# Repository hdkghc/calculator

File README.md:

[中文](README_zh.md)

# Calculator \| Operator Lambda

A scientific/graphical calculator firmware for Raspberry Pi Pico, with CAS (Computer Algebra System) and graphical display support.

PCB Preview ---->

**Status**: Under active development. Core CAS and display subsystem are partially implemented; basic arithmetic, expression parsing, and simplification are functional. Integration and matrix operations are in progress.

---

## Features

- CAS core: expression parsing, simplification, differentiation, integration (partial), rational arithmetic, symbolic manipulation.
- Display: 1.8" ST7735 TFT (160×128) with custom font rendering (ClassWiz-style fonts included).
- Input: 6×6 matrix keypad, debounced and mapped to mathematical operators.
- Storage: SD card support (WIP) for program/data loading.
- Modular design: separated CAS, display interface, input handling, and hardware abstraction.

---

## Hardware Requirements

- MCU: Raspberry Pi Pico (primary), Arduino Nano (power/control)
- Display: ST7735-based 1.8" TFT (SPI, with optional SD slot)
- Keypad: 6×6 matrix keypad (custom PCB – see `hardware/kicad` directory)
- Optional: SD card module (SPI)

Refer to `wiring.txt` (deprecated) and `hardware/kicad/` for schematics and PCB design. Gerber files are available in `hardware/gerber*.zip`.

---

## Project Structure

```
calculator/
├── CMakeLists.txt          # Build configuration
├── build.sh                # Convenience build script
├── inc/                    # Header files
│   ├── cas/                # CAS core (parser, simplifier, integrator, etc.)
│   └── dispinterface/      # Display abstraction
├── src/                    # Source files
│   ├── main.cpp            # Entry point
│   └── cas/                # CAS implementation
├── fonts/                  # Generated font data (ClassWiz style)
├── font2h/                 # Font conversion tools (font2h, preview)
├── hardware/               # PCB design (KiCad, Fritzing(deprecated), Gerber)
├── test/                   # Unit tests (CAS functions)
├── resources/              # Images (logo, PCB preview)
└── LICENSE                 # GPLv3
```

---

## Build Instructions

1. Install the [Raspberry Pi Pico SDK](https://github.com/raspberrypi/pico-sdk) and toolchain (arm-none-eabi-g++, CMake).
2. Clone this repository:
   ```
   git clone https://github.com/hdkghc/calculator.git
   cd calculator
   ```
3. Build:
   - Recommended: run `./build.sh` (automates CMake configuration and build).
   - Manual:
     ```
     mkdir build && cd build
     cmake ..
     make
     ```
4. Flash: drag the generated `.uf2` file to your Pico's mass storage device, or use `picotool`.

---

## Dependencies

- Raspberry Pi Pico SDK (required)
- C++17 compiler (`arm-none-eabi-g++`)

---

## License

This project is licensed under the **GNU General Public License v3.0**.  
See [LICENSE](LICENSE) for details.

---

## Disclaimer

This is an amateur, non-commercial open‑source project. All hardware and software are provided “as is”, without any warranty. The author assumes no liability for any damage or injury resulting from the use, assembly, or modification of this project.

---

## Contributing

Contributions are welcome! Please read [CONTRIBUTING.md](CONTRIBUTING.md) for guidelines.

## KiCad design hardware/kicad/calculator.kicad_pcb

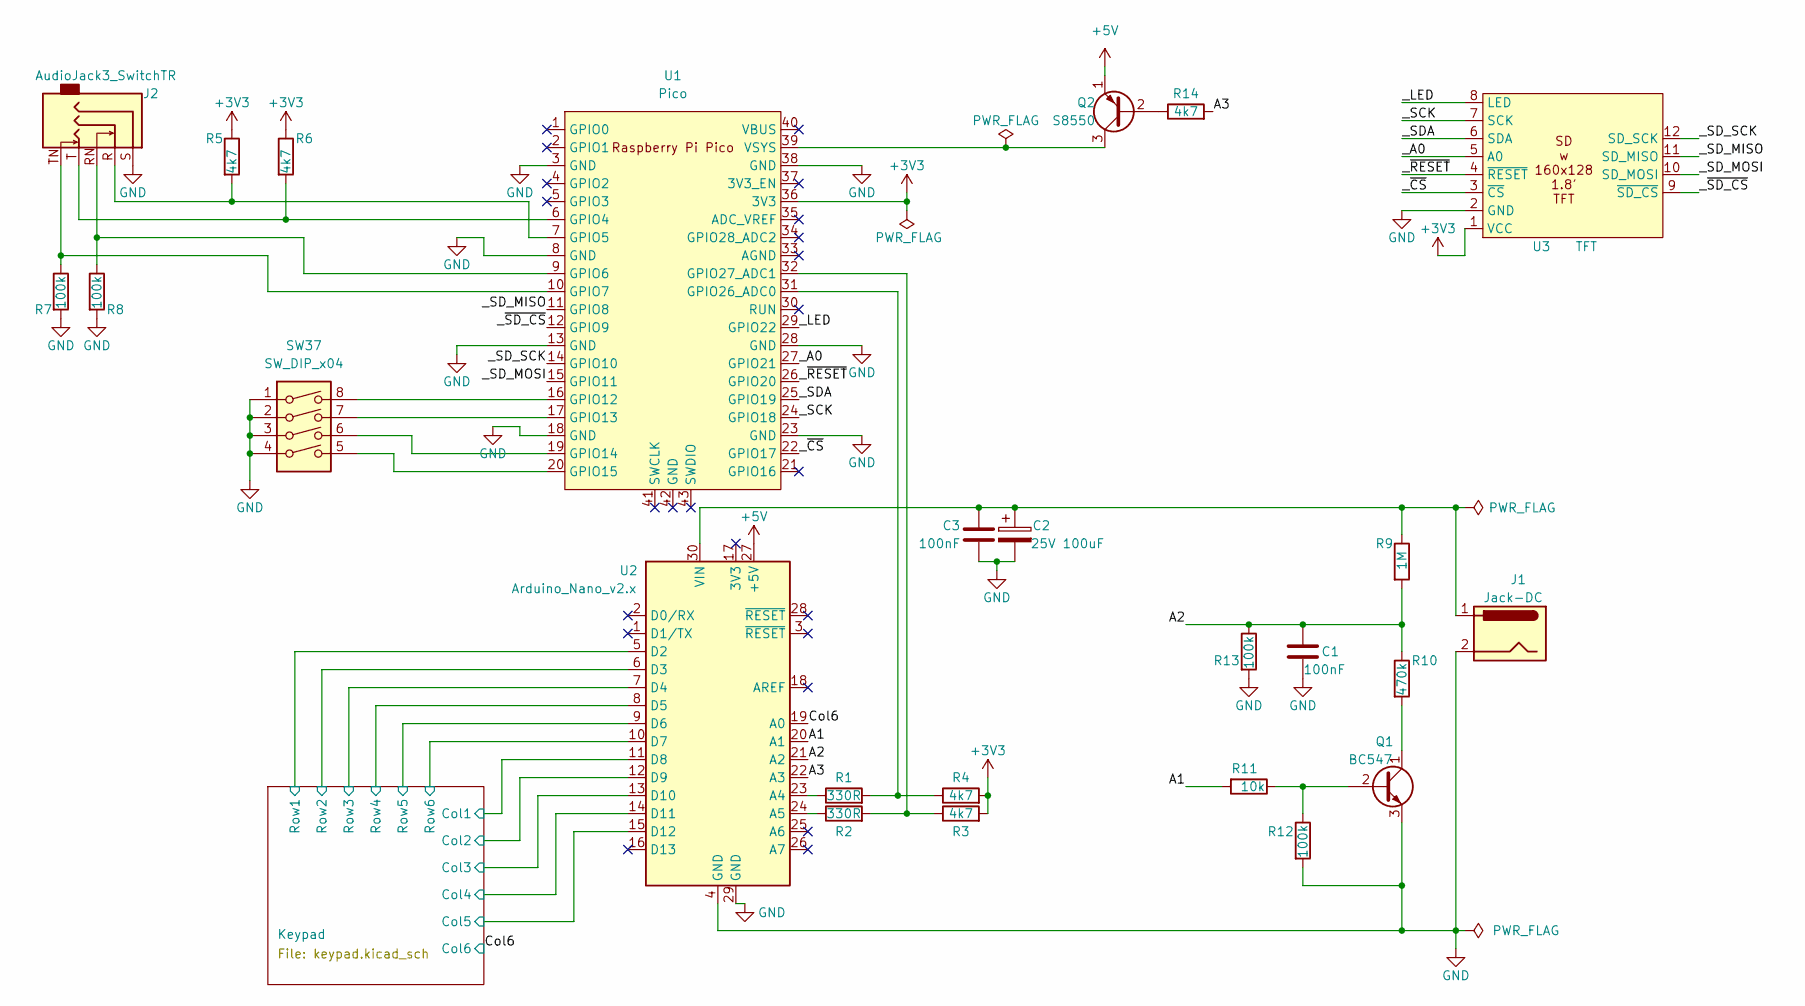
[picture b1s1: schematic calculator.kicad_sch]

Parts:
C1: 100nF; C_Disc_D6.0mm_W2.5mm_P5.00mm
C2: 25V 100uF; CP_Radial_D8.0mm_P3.50mm
C3: 100nF; C_Disc_D7.0mm_W2.5mm_P5.00mm
J1: Jack-DC; BarrelJack_Kycon_KLDX-0202-xC_Horizontal
J2: AudioJack3_SwitchTR; Jack_3.5mm_CUI_SJ1-3525N_Horizontal
Q1: BC547; TO-92_Inline
Q2: S8550; TO-92_Inline
R1, R2: 330R; R_Axial_DIN0207_L6.3mm_D2.5mm_P10.16mm_Horizontal
R3, R4, R5, R6, R14: 4k7; R_Axial_DIN0207_L6.3mm_D2.5mm_P10.16mm_Horizontal
R7, R8, R12, R13: 100k; R_Axial_DIN0207_L6.3mm_D2.5mm_P10.16mm_Horizontal
R9: 1M; R_Axial_DIN0207_L6.3mm_D2.5mm_P10.16mm_Horizontal
R10: 470k; R_Axial_DIN0207_L6.3mm_D2.5mm_P10.16mm_Horizontal
R11: 10k; R_Axial_DIN0207_L6.3mm_D2.5mm_P10.16mm_Horizontal
SW37: SW_DIP_x04; SW_DIP_SPSTx04_Slide_6.7x11.72mm_W7.62mm_P2.54mm_LowProfile
U1: Pico; RPi_Pico_SMD_TH
U2: Arduino_Nano_v2.x; Arduino_Nano
U3: TFT; MSP1803_TFT_12pin

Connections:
+3V3: R3.2, R4.2, R5.1, R6.1, U1.36 (3V3), U3.1 (VCC)
+5V: Q2.1 (E), U2.27 (+5V)
/A1: R11.2, U2.20 (A1)
/A2: C1.1, R9.2, R10.1, R13.1, U2.21 (A2)
/A3: R14.2, U2.22 (A3)
/Col6: U2.19 (A0); also elsewhere on the board
/Keypad/Col1: U2.11 (D8); also elsewhere on the board
/Keypad/Col2: U2.12 (D9); also elsewhere on the board
/Keypad/Col3: U2.13 (D10); also elsewhere on the board
/Keypad/Col4: U2.14 (D11); also elsewhere on the board
/Keypad/Col5: U2.15 (D12); also elsewhere on the board
/Keypad/Row1: U2.5 (D2); also elsewhere on the board
/Keypad/Row2: U2.6 (D3); also elsewhere on the board
/Keypad/Row3: U2.7 (D4); also elsewhere on the board
/Keypad/Row4: U2.8 (D5); also elsewhere on the board
/Keypad/Row5: U2.9 (D6); also elsewhere on the board
/Keypad/Row6: U2.10 (D7); also elsewhere on the board
/_A0: U1.27 (GPIO21), U3.5 (A0)
/_LED: U1.29 (GPIO22), U3.8 (LED)
/_SCK: U1.24 (GPIO18), U3.7 (SCK)
/_SDA: U1.25 (GPIO19), U3.6 (SDA)
/_SD_MISO: U1.11 (GPIO8), U3.11 (SD_MISO)
/_SD_MOSI: U1.15 (GPIO11), U3.10 (SD_MOSI)
/_SD_SCK: U1.14 (GPIO10), U3.12 (SD_SCK)
/_~CS: U1.22 (GPIO17), U3.3 (~CS)
/_~RESET: U1.26 (GPIO20), U3.4 (~RESET)
/_~SD_CS: U1.12 (GPIO9), U3.9 (~SD_CS)
GND: C1.2, C2.2, C3.1, J1.2, J2.S, Q1.3 (E), R7.2, R8.2, R12.2, R13.2, SW37.1, SW37.2, SW37.3, SW37.4, U1.3 (GND), U1.8 (GND), U1.13 (GND), U1.18 (GND), U1.23 (GND), U1.28 (GND), U1.38 (GND), U2.4 (GND), U2.29 (GND), U3.2 (GND)
unnamed: Q1.2 (B), R11.1, R12.1
unnamed: Q1.1 (C), R10.2
unnamed: Q2.2 (B), R14.1
unnamed: Q2.3 (C), U1.39 (VSYS)
unnamed: J2.T, R6.2, U1.6 (GPIO4)
unnamed: J2.R, R5.2, U1.7 (GPIO5)
unnamed: J2.RN, R8.1, U1.9 (GPIO6)
unnamed: J2.TN, R7.1, U1.10 (GPIO7)
unnamed: SW37.8, U1.16 (GPIO12)
unnamed: SW37.7, U1.17 (GPIO13)
unnamed: SW37.6, U1.19 (GPIO14)
unnamed: SW37.5, U1.20 (GPIO15)
unnamed: R1.2, R4.1, U1.31 (GPIO26_ADC0)
unnamed: R2.2, R3.1, U1.32 (GPIO27_ADC1)
unnamed: R1.1, U2.23 (A4)
unnamed: R2.1, U2.24 (A5)
unnamed: C2.1, C3.2, J1.1, R9.1, U2.30 (VIN)

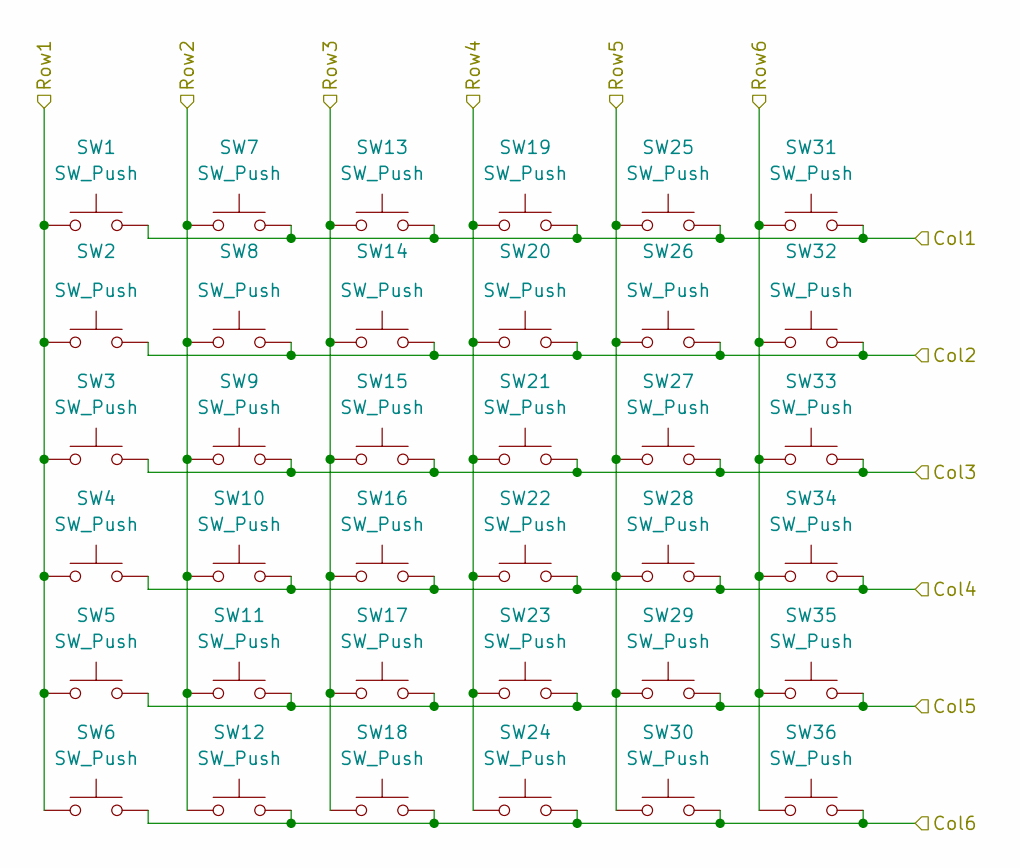
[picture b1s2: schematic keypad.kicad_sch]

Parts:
SW1, SW2, SW3, SW4, SW5, SW6, SW7, SW8, SW9, SW10, SW11, SW12, SW13, SW14, SW15, SW16, SW17, SW18, SW19, SW20, SW21, SW22, SW23, SW24, SW25, SW26, SW27, SW28, SW29, SW30, SW31, SW32, SW33, SW34, SW35, SW36: SW_Push; SW_PUSH_6mm

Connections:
/Col6: SW6.2, SW12.2, SW18.2, SW24.2, SW30.2, SW36.2; also elsewhere on the board
/Keypad/Col1: SW1.2, SW7.2, SW13.2, SW19.2, SW25.2, SW31.2; also elsewhere on the board
/Keypad/Col2: SW2.2, SW8.2, SW14.2, SW20.2, SW26.2, SW32.2; also elsewhere on the board
/Keypad/Col3: SW3.2, SW9.2, SW15.2, SW21.2, SW27.2, SW33.2; also elsewhere on the board
/Keypad/Col4: SW4.2, SW10.2, SW16.2, SW22.2, SW28.2, SW34.2; also elsewhere on the board
/Keypad/Col5: SW5.2, SW11.2, SW17.2, SW23.2, SW29.2, SW35.2; also elsewhere on the board
/Keypad/Row1: SW1.1, SW2.1, SW3.1, SW4.1, SW5.1, SW6.1; also elsewhere on the board
/Keypad/Row2: SW7.1, SW8.1, SW9.1, SW10.1, SW11.1, SW12.1; also elsewhere on the board
/Keypad/Row3: SW13.1, SW14.1, SW15.1, SW16.1, SW17.1, SW18.1; also elsewhere on the board
/Keypad/Row4: SW19.1, SW20.1, SW21.1, SW22.1, SW23.1, SW24.1; also elsewhere on the board
/Keypad/Row5: SW25.1, SW26.1, SW27.1, SW28.1, SW29.1, SW30.1; also elsewhere on the board
/Keypad/Row6: SW31.1, SW32.1, SW33.1, SW34.1, SW35.1, SW36.1; also elsewhere on the board

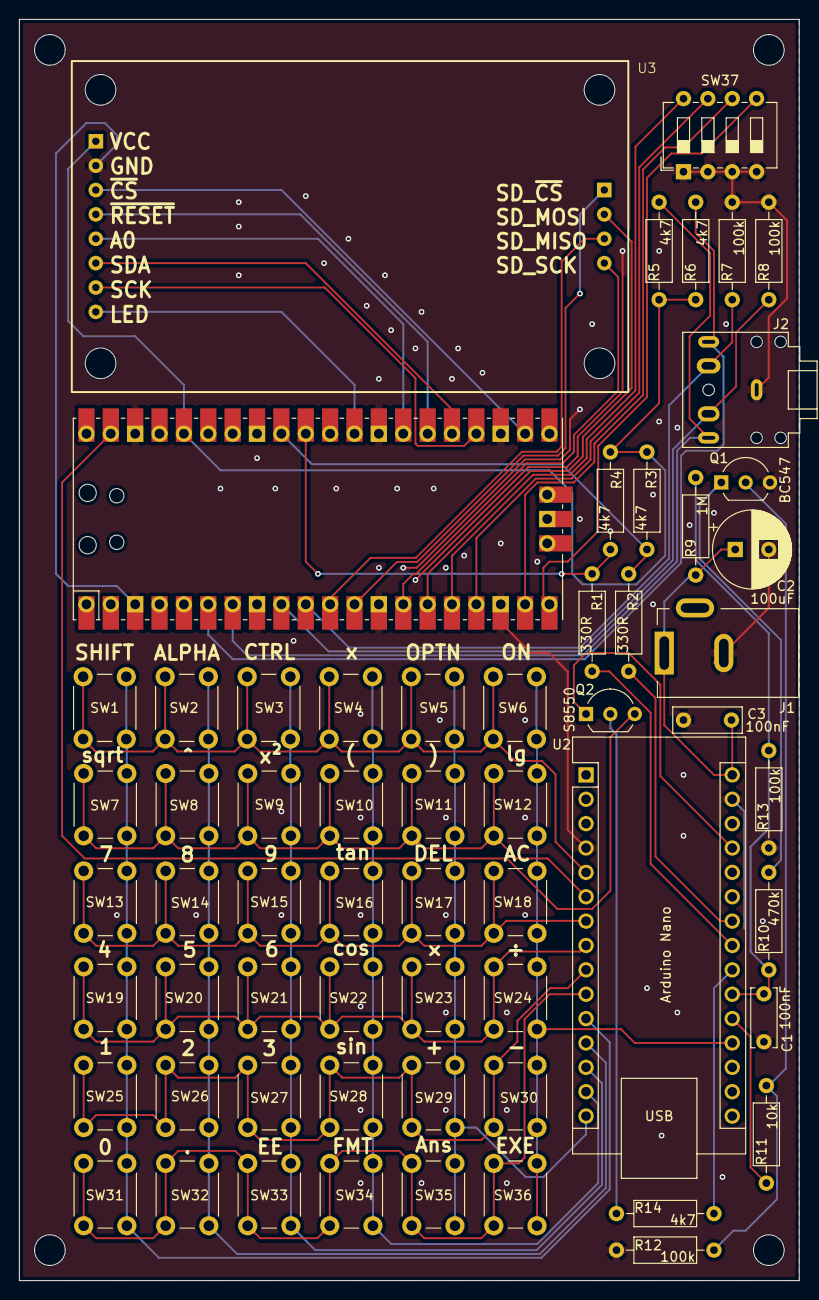
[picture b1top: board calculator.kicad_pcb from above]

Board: 2 copper layers, 81.3 x 131.4 mm, 61 parts (0 on the bottom side), 45 nets.

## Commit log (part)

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2026-04-20 new file: .gitignore new file: CMakeLists.txt new file: build.sh new file: main.cpp copy file: pico_sdk_import.cmake
2026-04-20 modified: CMakeLists.txt
2026-04-20 modified: .gitignore new file: .gitmodules modified: CMakeLists.txt
2026-04-25 modified: .gitignore new file: wiring.txt
2026-04-25 modified: .gitignore modified: CMakeLists.txt modified: build.sh new file: font2h/compile.sh new file: font2h/font2h.cpp new file: font2h/fonts/ClassWizCWDisplay-Regular.otf new file: font2h/fonts/Cl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
2026-04-25 modified: .gitignore modified: build.sh modified: font2h/compile.sh deleted: font2h/pvw.cpp new file: inc/rgb.h modified: main.cpp new file: test_fonts/CMakeLists.txt new file: test_fonts/testbuild.s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
2026-04-25 modified: CMakeLists.txt modified: build.sh modified: font2h/compile.sh modified: main.cpp deleted: test_fonts/CMakeLists.txt deleted: test_fonts/testbuild.sh deleted: test_fonts/testmain.cpp
2026-04-25 new file: CONTRIBUTING.md new file: LICENSE new file: README.md modified: main.cpp
2026-04-25 modified: LICENSE
2026-04-26 modified: .gitignore modified: CMakeLists.txt modified: main.cpp modified: pico-st7735/lib-st7735/include/ST7735_TFT.h modified: pico-st7735/lib-st7735/src/ST7735_TFT.c
2026-05-17 modified: .gitmodules modified: CMakeLists.txt modified: inc/rgb.h deleted: main.cpp deleted: pico-st7735/ new file: src/display.cpp new file: src/main.cpp
2026-05-17 modified: CMakeLists.txt renamed: src/display.cpp -> inc/display.hpp modified: inc/rgb.h modified: src/main.cpp
2026-05-23 new file: inc/cas/intg.hpp modified: inc/display.hpp modified: inc/rgb.h modified: src/main.cpp
2026-05-23 modified: inc/cas/intg.hpp
2026-05-23 new file: inc/cas/gcd.hpp modified: inc/cas/intg.hpp modified: inc/display.hpp modified: inc/rgb.h modified: src/main.cpp
2026-05-23 modified: inc/cas/intg.hpp new file: inc/cas/rational.hpp
2026-05-24 bug fix modified: .gitignore new file: compile_test.sh modified: inc/cas/intg.hpp new file: test/testintg.cpp
2026-05-24 modified: test/testintg.cpp
2026-05-30 modified: inc/cas/intg.hpp modified: test/testintg.cpp
2026-06-06 Update README to include generation note
    Added a note indicating that the README was generated by GitHub Copilot.
2026-06-06 update: README.md
2026-06-26 Bug fix: class Intg constructor & operator+ modified: inc/cas/intg.hpp new file: test/test_intg_init.cpp new file: test/test_random_intg.cpp modified: test/testintg.cpp
2026-06-26 added basic rational calculations modified: inc/cas/intg.hpp modified: inc/cas/rational.hpp
2026-06-26 new file: inc/cas/exptree.hpp
2026-06-27 modified: inc/cas/exptree.hpp
2026-06-27 new file: inc/cas/expdef.hpp
2026-06-27 + Scientific constants modified: inc/cas/expdef.hpp
2026-06-27 + constant definitions new file: inc/cas/constdef.hpp modified: inc/cas/expdef.hpp
2026-06-27 modified: inc/cas/exptree.hpp new file: inc/cas/treesimp.hpp
2026-06-27 Expression tree simplify logic & integer sqrt modified: inc/cas/intg.hpp modified: inc/cas/rational.hpp modified: inc/cas/treesimp.hpp
2026-06-27 Upd: expression tree simplify logic modified: inc/cas/expdef.hpp modified: inc/cas/treesimp.hpp
2026-06-27 Upd comment modified: inc/cas/treesimp.hpp
2026-06-27 upd sqrt modified: inc/cas/intg.hpp
2026-06-28 modified: inc/cas/treesimp.hpp
2026-06-28 split treesimp.hpp into submodules new file: inc/cas/simp/exptreepool.hpp new file: inc/cas/simp/simp_internal.hpp new file: inc/cas/simp/simputil.hpp modified: inc/cas/treesimp.hpp new file: src/cas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
2026-06-28 complex number support modified: src/cas/simp/simp_arith.cpp modified: src/cas/simp/simp_log.cpp modified: src/cas/simp/simp_misc.cpp modified: src/cas/simp/simp_trig.cpp
2026-06-28 matrix & vector support modified: inc/cas/intg.hpp modified: inc/cas/simp/simputil.hpp modified: inc/cas/treesimp.hpp modified: src/cas/simp/simp_arith.cpp new file: src/cas/simp/simp_complex.cpp new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
2026-06-28 Update .gitmodules, display.hpp and one other file
2026-06-28 new file: test/test_treesimp.cpp new file: test/treesimp.txt modified: compile_test.sh modified: inc/cas/gcd.hpp modified: inc/cas/intg.hpp modified: inc/cas/treesimp.hpp modified: src/cas/simp/simp_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
2026-06-28 Updated exptree simplifier modified: src/cas/simp/simp_number.cpp modified: test/treesimp.txt
2026-06-28 Upd modified: src/cas/simp/simp_arith.cpp modified: src/cas/simp/simp_log.cpp modified: src/cas/simp/simp_trig.cpp
2026-06-28 Upd exptree simplifier modified: inc/cas/simp/exptreepool.hpp modified: src/cas/simp/simp_arith.cpp modified: src/cas/simp/simp_hyper.cpp modified: src/cas/simp/simp_log.cpp modified: src/cas/simp/si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
2026-06-28 Bug fix double free in pol & rec & abs modified: src/cas/simp/simp_coord.cpp modified: src/cas/simp/simp_misc.cpp modified: test/treesimp.txt
2026-06-29 pol & rec update, support sqrt(3) / 3 -> 3^(-1/2) modified: src/cas/simp/simp_arith.cpp modified: src/cas/simp/simp_coord.cpp modified: src/cas/simp/simp_trig.cpp
2026-06-29 modified: compile_test.sh modified: src/cas/simp/simp_arith.cpp modified: src/cas/simp/simp_trig.cpp modified: test/treesimp.txt
2026-06-29 expand new file: inc/cas/expand.hpp modified: inc/cas/simp/exptreepool.hpp modified: inc/cas/treesimp.hpp new file: src/cas/expand.cpp modified: test/test_treesimp.cpp modified: test/treesimp.txt
2026-06-29 feat: vector normalization & matrix computation modified: inc/cas/expdef.hpp modified: inc/cas/treesimp.hpp modified: src/cas/simp/simp_arith.cpp modified: src/cas/simp/simp_core.cpp modified: src/ca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
2026-06-29 fix: bug fix double free & heap use after free modified: src/cas/simp/simp_matrix.cpp
2026-06-29 Upd keypad layout modified: inc/cas/expdef.hpp new file: inc/cas/parser.hpp new file: keypad.md
2026-06-30 new file: inc/keypad.hpp modified: keypad.md
2026-06-30 new file: functions.txt modified: inc/cas/expdef.hpp modified: inc/keypad.hpp modified: keypad.md modified: src/cas/simp/simp_number.cpp modified: test/test_treesimp.cpp
2026-06-30 modified: inc/keypad.hpp new file: inc/keypad_handler.hpp modified: test/test_treesimp.cpp
2026-06-30 modified: inc/keypad.hpp modified: inc/keypad_handler.hpp new file: test/test_keypad.cpp

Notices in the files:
hardware/kicad/calculator.kicad_pcb:
Copyright (c) 2026 hdkghc
